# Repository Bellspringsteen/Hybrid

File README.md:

## Hybrid Vehicle Project

This is not meant as a easily reproducable or educational guide/project for building your own system. Maybe one day. It is mostly a collection of information, with large sections missing, of my personal project.

##Hybrid V1

##Hybrid V2

###On the Road

###How it Works

View the Steps to Making It

* [Step 1- The Idea](http://blog.labsbell.com/blog/HybridStep1/)
* [Step 2- Input and Output](http://blog.labsbell.com/blog/HybridStep2/)
* [Step 3- Mechanical](http://blog.labsbell.com/blog/HybridStep3/)
* [Step 4- Electrical](http://blog.labsbell.com/blog/HybridStep4/)
* [Step 5- Hybrid Control Unit](http://blog.labsbell.com/blog/HybridStep5/)
* [Step 6- Software](http://blog.labsbell.com/blog/HybridStep6/)
* [Step 7- Testing](http://blog.labsbell.com/blog/HybridStep7/)

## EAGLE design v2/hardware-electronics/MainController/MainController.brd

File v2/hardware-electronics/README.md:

# Hardware Electronics Section
## V2 Parrallel Hybrid Supercapacitor Scooter

## The Messy Controler and Supercap Setup

## Controller Outside

## Controller Topside

## Controller Underside

Controller Schematic is Located in /MainController/ and the bike side schematic is in /VehicleSchematic/

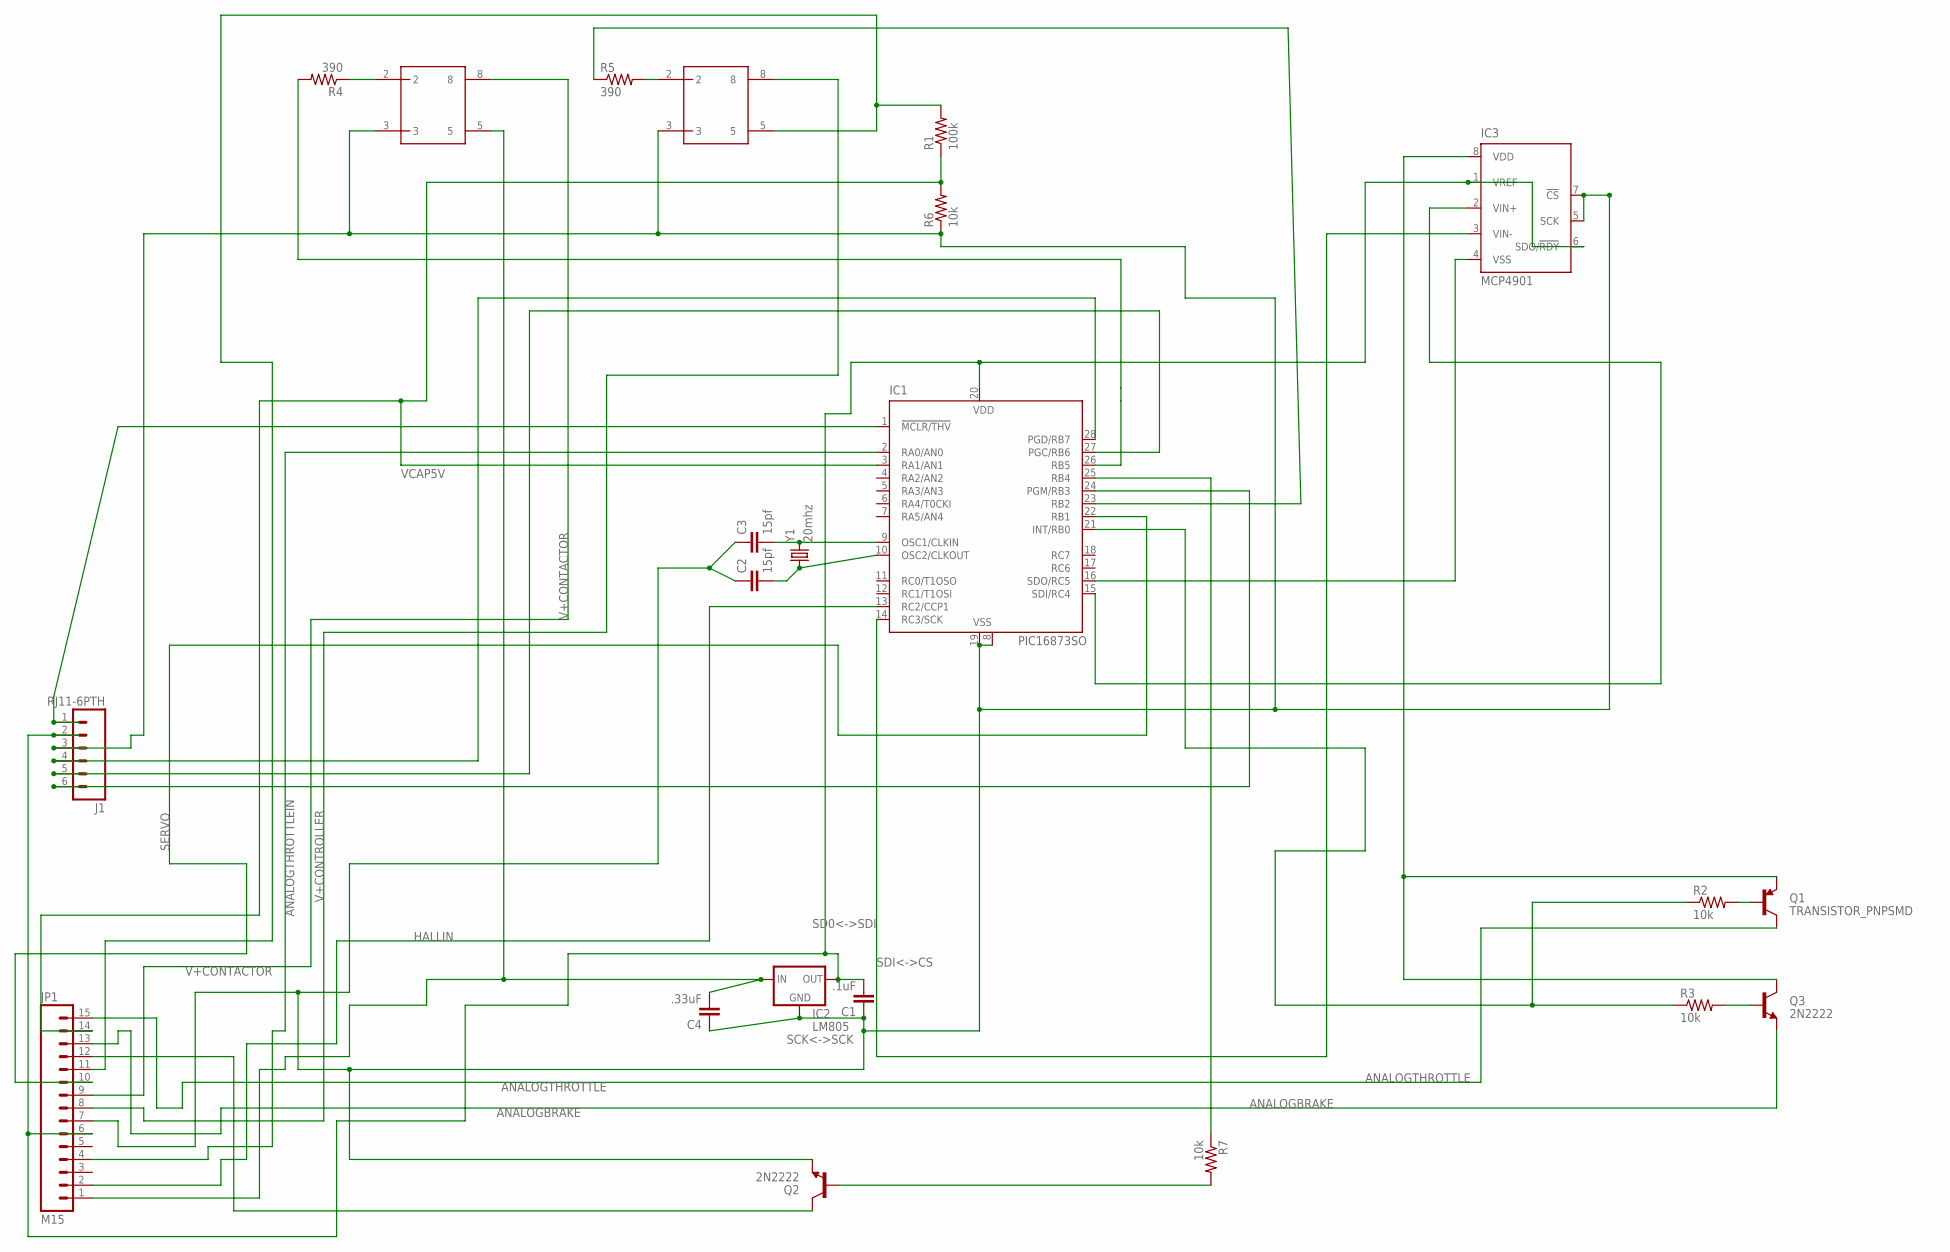
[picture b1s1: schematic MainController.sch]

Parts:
C1: .1uF; 0402-CAP
C2, C3: 15pf; 0402-CAP
C4: .33uF; 0402-CAP
IC1: PIC16873SO; SO28W
IC2: LM805; 78XXL
IC3: MCP4901; SO-08
J1: RJ11-6PTH; RJ11-6
JP1: M15; 1X15
Q1: TRANSISTOR_PNPSMD; SOT23-3
Q2: 2N2222; SOT23-3
Q3: 2N2222; SOT23
R1: 100k; 0805
R2, R3, R6, R7: 10k; 0805
R4, R5: 390; 0805
U$14, U$18: OPTO_DARL_6N138S; 8-SMD
Y1: 20mhz; HC49US

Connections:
ANALOGBRAKE: JP1.13, Q3.2 (E)
ANALOGTHROTTLE: JP1.15, Q1.3 (C)
ANALOGTHROTTLEIN: IC1.2 (RA0/AN0), JP1.4
GROUND: C1.1, C2.1, C3.1, C4.1, IC1.8 (VSS), IC1.19 (VSS), IC2.GND, IC3.5 (SCK), IC3.7 (!CS), J1.3, JP1.7, Q2.2 (E), R6.1, U$14.3, U$18.3
HALLIN: IC1.13 (RC2/CCP1), JP1.2
unnamed: R4.1, U$14.2
unnamed: IC1.1 (!MCLR/THV), J1.1
unnamed: IC1.28 (PGD/RB7), J1.4
unnamed: IC1.27 (PGC/RB6), J1.5
unnamed: C3.2, IC1.9 (OSC1/CLKIN), Y1.2
unnamed: C2.2, IC1.10 (OSC2/CLKOUT), Y1.1
unnamed: IC3.8 (VDD), Q1.2 (E), Q3.3 (C)
unnamed: IC1.26 (RB5), R4.2
unnamed: IC1.23 (RB2), R5.1
unnamed: R5.2, U$18.2
unnamed: Q3.1 (B), R3.2
unnamed: JP1.12, Q2.3 (C)
unnamed: Q2.1 (B), R7.2
unnamed: IC1.21 (INT/RB0), R2.1, R3.1
unnamed: IC1.25 (RB4), R7.1
unnamed: Q1.1 (B), R2.2
unnamed: IC1.24 (PGM/RB3), J1.6
unnamed: JP1.11, R1.2, U$18.5
unnamed: C4.2, IC2.IN, JP1.1, U$14.5
unnamed: C1.2, IC1.20 (VDD), IC2.OUT, IC3.1 (VREF), IC3.6 (SDO/!RDY), J1.2, JP1.6
SCK<->SCK: IC1.14 (RC3/SCK), IC3.3 (VIN-)
SD0<->SDI: IC1.16 (SDO/RC5), IC3.4 (VSS)
SDI<->CS: IC1.15 (SDI/RC4), IC3.2 (VIN+)
SERVO: IC1.22 (RB1), JP1.10
V+CONTACTOR: JP1.9, U$14.8
V+CONTROLLER: JP1.8, U$18.8
VCAP5V: IC1.3 (RA1/AN1), JP1.14, R1.1, R6.2

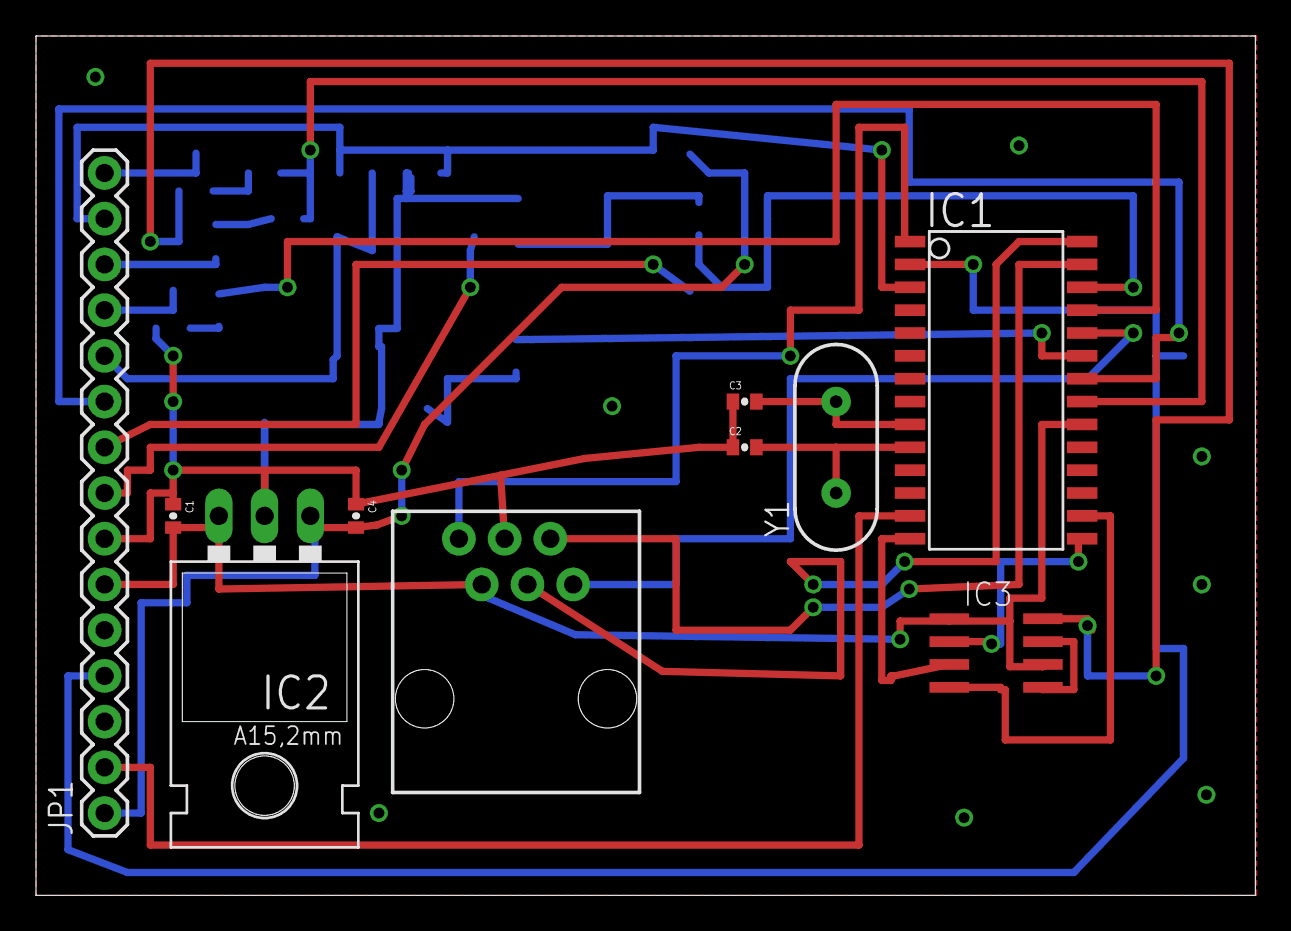
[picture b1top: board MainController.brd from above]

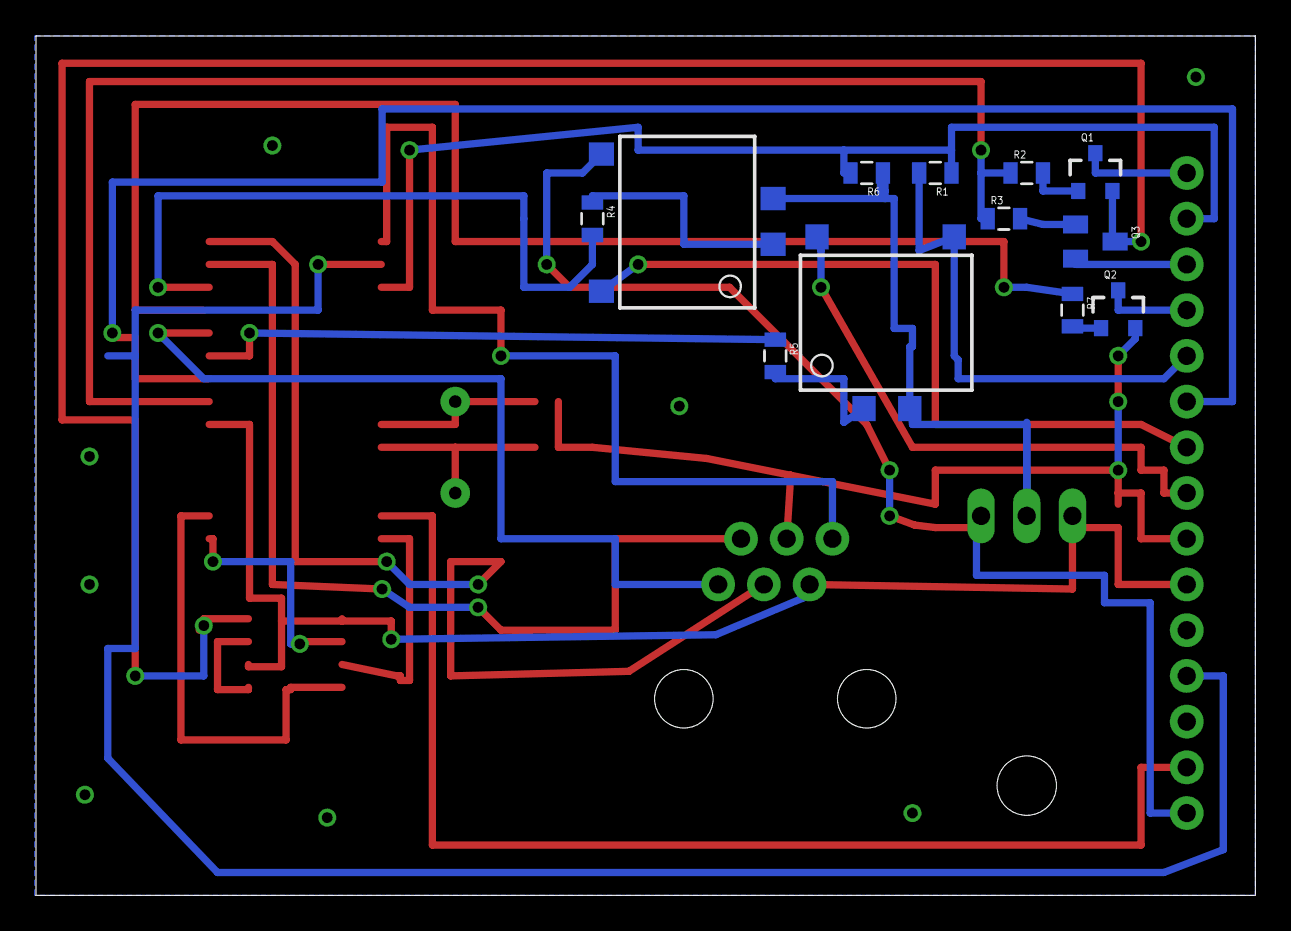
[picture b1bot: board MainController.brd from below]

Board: 2 copper layers, 67.7 x 47.7 mm, 22 parts (12 on the bottom side), 32 nets.

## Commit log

2004-07-08 changing the servo position to match the new version of the servo throttle holder. In addition fixed up the servo test so that it swipped through the left_position to right_position region
2012-07-02 This is the current version of the PIC controller for the hybrid v2 really just bits and pieces getting in order before we tie everything together.
2012-07-04 Servo Component
2012-07-04 Everything Added Together
2012-08-03 Wrote out all input outputs and laid out algorithm in comments
2012-08-13 Adding some pin informtion
2012-10-13 This version has all the timing components inserted. It takes the input analog voltage on the Analog Throttle and sweeps the servo back and forth as directed by the analog voltage.
2012-10-20 This version has the speed input being output as an analog value on the servo, still have to test with the motor controller
2012-10-20 Adding back the analog sensing to make sure that doesnt fuck anything up
2012-11-15 Version running and confirmed output of analog voltage and the turning of the servo
2012-11-24 Finished testing the analog voltage output from the RED controller.
2012-11-24 adding mcp file
2012-11-24 State where the servo output mirrors the analog input 1 to 1 follower
2012-11-24 State where the analog voltage output mirrors the analog voltage input 1 to 1
2012-11-24 Adding begginings of the PID
2012-12-01 Changes to account for limited range of servo. Succesfully controlled servo on throttle body from the electric throttle input.
2012-12-08 Confirmed working of control over Electric Controller from PIC. Switched direction of servo so that it goes high to low. ( Also put the springin the servo so that the cable operated throttle works) T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
2012-12-22 On the way to getting braking/charging to work. Actually kind of sucked because the electrical controller is still driving the braking circuit high
2013-01-05 fixing merge
2013-01-05 PID playing, how to test
2013-01-06 Damn MCP ADC was using PIN_B4 Took me hours of searching to realize this was the problem
2013-01-27 braking worked, now doing speed feedback loop
2013-02-03 Fixed up the speed calculation, now a number from 0 - 1024
2013-02-17 Proportional Control System working on Speed Controller
2013-03-04 Added PID into the speed controller. however it is now very unstable after the addition of the integration
2013-03-17 Fixed the integrator and derivative terms. 1 i overlooked that fact that the floating point numbers were being converted by the SCALING_FACTOR to non floating point. Furthermore the addition of a int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
2013-05-03 a little housekeeping before the final push
2013-05-08 about to add checks for voltage etc
2013-05-11 This configuration when started after ICE was running caused breaking
2013-05-11 Actually the trick breaking is not required. Started electrical before ice and still charged.
2013-05-11 Fighting with a problem on breaking. This configuration works but ELECthrottle is hard coded to 200
2013-05-11 The problem was that there does have to be a acceleration event before a breaking event. So that some of my testing was not real. Also removing the unsigned cast might have helped
2013-05-24 Adding state enum
2013-05-31 Adding test outputs
2013-06-01 finished doing tests
2013-06-05 Added more to the state machine
2013-06-08 Fixed problem with power not going off when throttle off. Also have to devise mechanism besides runaway to decrease ICE throttle. Lastly the servo suddenly has a lot more room
2013-06-21 updating
2013-06-28 Trying to determine why device is restarting
2013-06-28 adding the Test suite back in.
2013-06-29 This is the code running durring the first test on the streets
2013-08-03 This is the firmware running on the August 3rd Test
2013-08-24 changes made after the ride of 8/24/13. Need to make sure the throttle is being fully shut off. Otherwise get into a state where the electric is driving but being bogged down by the load of the engin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
2013-09-14 Setting the right servo value so low caused problems with starting the ICE durring the transition from ICE to electric
2013-10-29 Adding support for both Hardware Boards Version 1 and 2
2013-11-07 Missing the controller turn on switch in the board revision checks
2013-11-08 adding the switch to enable simple analog throttle to ICE throttle
2013-11-15 making changes to accomodate weak hybrid mode
2013-11-15 Electric Controller Switch is really whether the controller is accelerating/decelerating. Was forgetting to set both contactors.
2013-11-29 Adding the startup items in the test, both boards working
2013-12-30 removing delays in preprocessor if defs
2014-01-03 Adding gitignore, taken this long
2014-01-03 Cleaning up, moving software to software folder
2014-01-03 More items for the git ignore
2014-01-03 More Clean Up
2014-01-03 Adding images
2014-01-11 Problem:After long periods at full throttle, the caps are full up and the speed is still high. Because the wheel is powered, the caps are charging even under throttle. This could lead to the caps get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
2014-01-13 Adding some a readme or two
2014-01-13 How to github images in readmes work?
2014-02-22 Reformatted, and add smoothing to throttle delivery for electric. SO it doesnt try killing me like the last test ride
2014-03-15 Very smooth test run today of a couple of miles. Only addition is to completely shut off electric if throttle is closed
2014-10-27 Changing Readme

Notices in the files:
parts and their libraries:
SparkFun: Licensing: CC v3.0 Share-Alike You are welcome to use this library for commercial purposes.
